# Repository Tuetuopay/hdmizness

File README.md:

# hdmizness

A business card that runs Linux and that has an HDMI output.

## Project layout

```
.
+- documentation       - docs for various chips and boards used
+- graphics            - various graphic files used for the hardware design
+- hardware            - home of the hardware design files
|  `- licheedmi        - PoC board that leverages a Lichee Pi Nano to test the concept
|                        of a pcb-only hdmi female connector
`- software            - everything related to the software running on those boards
```

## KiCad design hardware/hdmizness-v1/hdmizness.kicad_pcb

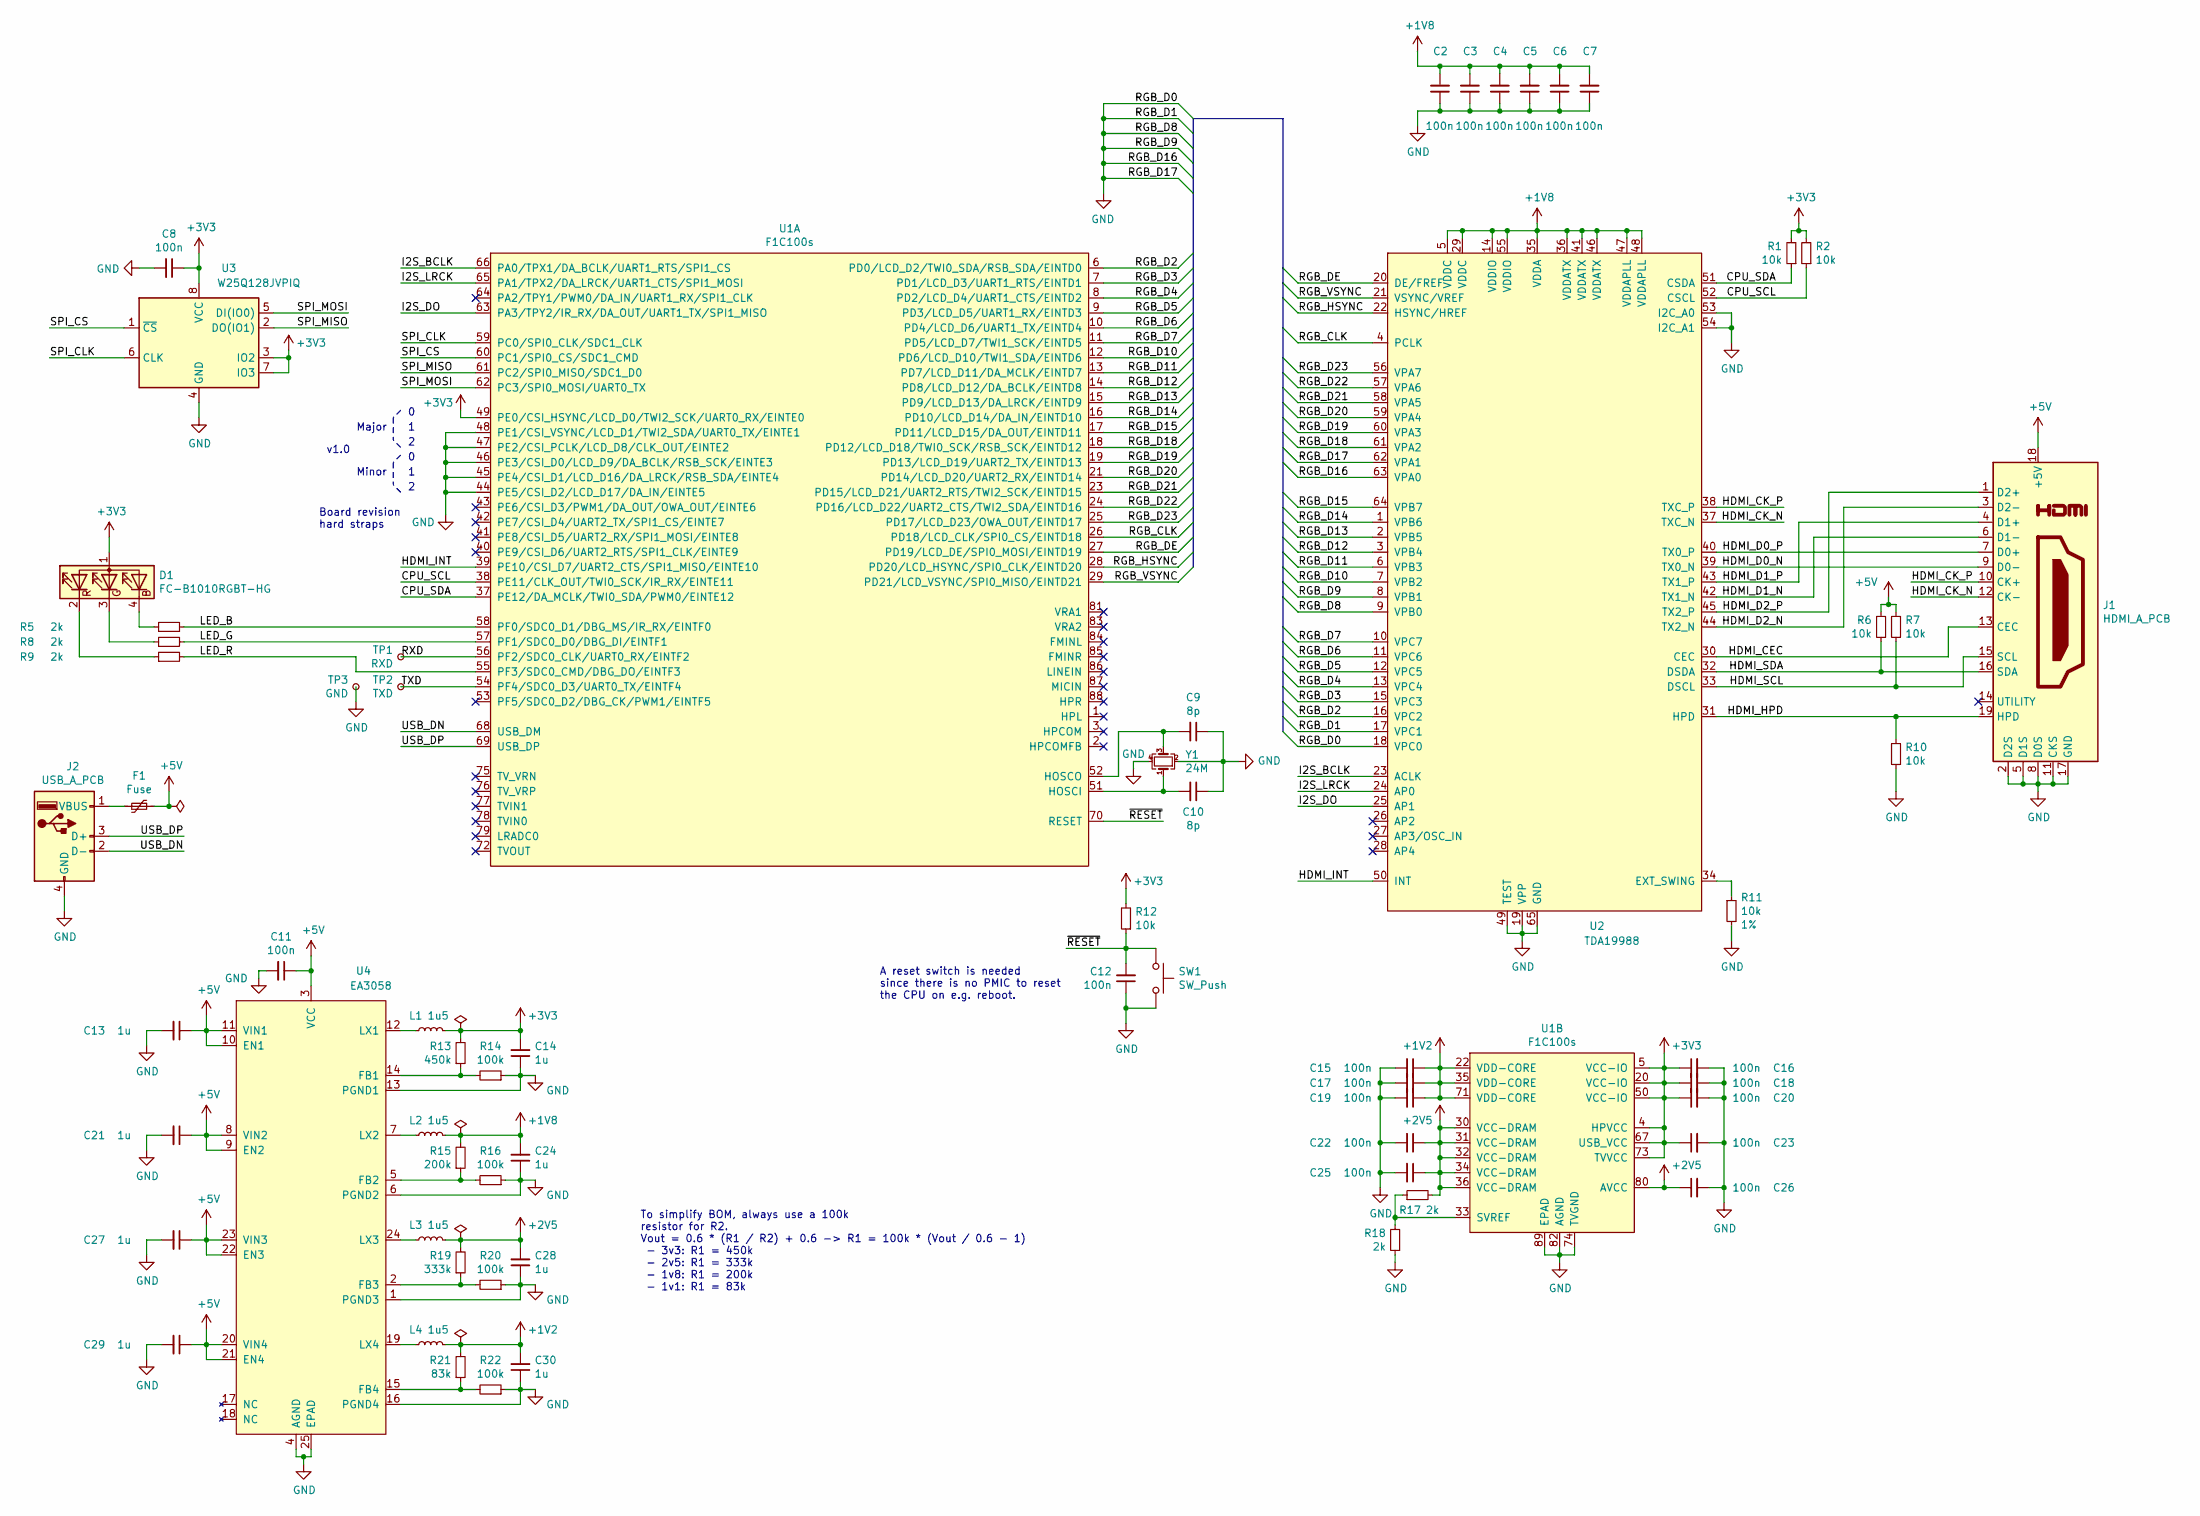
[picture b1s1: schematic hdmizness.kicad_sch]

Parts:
C2, C3, C4, C5, C6, C7, C8, C11, C12, C15, C16, C17, C18, C19, C20, C22, C23, C25, C26: 100n; C_0402_1005Metric; MFR P/N CL05B104KO5NNNC; LCSC P/N C1525
C9, C10: 8p; C_0402_1005Metric; MFR P/N CL05C080CB5NNNC; LCSC P/N C318586
C13, C14, C21, C24, C27, C28, C29, C30: 1u; C_0402_1005Metric; MFR P/N CL05A105KQ5NNNC; LCSC P/N C107372
D1: FC-B1010RGBT-HG; PLCC1010
F1: Fuse; Fuse_0603_1608Metric; MFR P/N 06H1100D; LCSC P/N C182303
J1: HDMI_A_PCB
J2: USB_A_PCB
L1, L2, L3, L4: 1u5; L_Vishay_IHHP-0806; MFR P/N CIGT201610UM1R5MNE; LCSC P/N C307630
R1, R2, R6, R7, R10, R12: 10k; R_0402_1005Metric; MFR P/N CR-02FL6---10K; LCSC P/N C406733
R5, R8, R9, R17, R18: 2k; R_0402_1005Metric; MFR P/N RC-02W2001FT; LCSC P/N C304583
R11: 10k; R_0402_1005Metric; Tolerance 1%; MFR P/N CR-02FL6---10K; LCSC P/N C406733
R13: 450k; R_0402_1005Metric; MFR P/N 0402WGF4503TCE; LCSC P/N C407681
R14, R16, R20, R22: 100k; R_0402_1005Metric; MFR P/N RC-02W1003FT; LCSC P/N C258090
R15: 200k; R_0402_1005Metric; MFR P/N WR04X2003FTL; LCSC P/N C305297
R19: 333k; R_0402_1005Metric; MFR P/N WR04X3323FTL; LCSC P/N C172051
R21: 83k; R_0402_1005Metric; MFR P/N RC-02W8202FT; LCSC P/N C304638
SW1: SW_Push; 1TS028A-2400-0603-CT; MFR P/N 1TS028A-2400-0603-CT; LCSC P/N C481994
TP1: RXD; TestPoint_Pad_1.0x1.0mm
TP2: TXD; TestPoint_Pad_1.0x1.0mm
TP3: GND; TestPoint_Pad_1.0x1.0mm
U1: F1C100s; QFN-88_EP_10x10_Pitch0.4mm
U2: TDA19988; QFN-64-1EP_9x9mm_P0.5mm_EP4.7x4.7mm
U3: W25Q128JVPIQ; WSON-8-1EP_6x5mm_P1.27mm_EP3.4x4.3mm; MFR P/N W25Q128JVPIQ; LCSC P/N C190862
U4: EA3058; QFN-24-1EP_4x4mm_P0.5mm_EP2.6x2.6mm; MFR P/N EA3058QDR; LCSC P/N C575412
Y1: 24M; Crystal_SMD_2016-4Pin_2.0x1.6mm; MFR P/N CN4024M00009T8188011; LCSC P/N C708986

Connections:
+1V2: C15.1, C17.1, C19.1, C30.2, L4.2, R21.2, U1.22 (VDD-CORE), U1.35 (VDD-CORE), U1.71 (VDD-CORE)
+1V8: C2.2, C3.2, C4.2, C5.2, C6.2, C7.2, C24.2, L2.2, R15.2, U2.5 (VDDC), U2.14 (VDDIO), U2.29 (VDDC), U2.35 (VDDA), U2.36 (VDDATX), U2.41 (VDDATX), U2.46 (VDDATX), U2.47 (VDDAPLL), U2.48 (VDDAPLL), U2.55 (VDDIO)
+2V5: C22.1, C25.1, C26.1, C28.2, L3.2, R17.2, R19.2, U1.30 (VCC-DRAM), U1.31 (VCC-DRAM), U1.32 (VCC-DRAM), U1.34 (VCC-DRAM), U1.36 (VCC-DRAM), U1.80 (AVCC)
+3V3: C8.1, C14.2, C16.1, C18.1, C20.1, C23.1, D1.1 (A), L1.2, R1.2, R2.2, R12.2, R13.2, U1.4 (HPVCC), U1.5 (VCC-IO), U1.20 (VCC-IO), U1.49 (PE0/CSI_HSYNC/LCD_D0/TWI2_SCK/UART0_RX/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), U1.50 (VCC-IO), U1.67 (USB_VCC), U1.73 (TVVCC), U3.3 (IO2), U3.7 (IO3), U3.8 (VCC)
+5V: C11.1, C13.1, C21.1, C27.1, C29.1, F1.1, J1.18 (+5V), R6.2, R7.2, U4.3 (VCC), U4.8 (VIN2), U4.9 (EN2), U4.10 (EN1), U4.11 (VIN1), U4.20 (VIN4), U4.21 (EN4), U4.22 (EN3), U4.23 (VIN3)
/CPU_SCL: R2.1, U1.38 (PE11/CLK_OUT/TWI0_SCK/IR_RX/EINTE11), U2.52 (CSCL)
/CPU_SDA: R1.1, U1.37 (PE12/DA_MCLK/TWI0_SDA/PWM0/EINTE12), U2.51 (CSDA)
/HDMI_CEC: J1.13 (CEC), U2.30 (CEC)
/HDMI_CK_N: J1.12 (CK-), U2.37 (TXC_N)
/HDMI_CK_P: J1.10 (CK+), U2.38 (TXC_P)
/HDMI_D0_N: J1.9 (D0-), U2.39 (TX0_N)
/HDMI_D0_P: J1.7 (D0+), U2.40 (TX0_P)
/HDMI_D1_N: J1.6 (D1-), U2.42 (TX1_N)
/HDMI_D1_P: J1.4 (D1+), U2.43 (TX1_P)
/HDMI_D2_N: J1.3 (D2-), U2.44 (TX2_N)
/HDMI_D2_P: J1.1 (D2+), U2.45 (TX2_P)
/HDMI_HPD: J1.19 (HPD), R10.2, U2.31 (HPD)
/HDMI_INT: U1.39 (PE10/CSI_D7/UART2_CTS/SPI1_MISO/EINTE10), U2.50 (INT)
/HDMI_SCL: J1.15 (SCL), R7.1, U2.33 (DSCL)
/HDMI_SDA: J1.16 (SDA), R6.1, U2.32 (DSDA)
/I2S_BCLK: U1.66 (PA0/TPX1/DA_BCLK/UART1_RTS/SPI1_CS), U2.23 (ACLK)
/I2S_DO: U1.63 (PA3/TPY2/IR_RX/DA_OUT/UART1_TX/SPI1_MISO), U2.25 (AP1)
/I2S_LRCK: U1.65 (PA1/TPX2/DA_LRCK/UART1_CTS/SPI1_MOSI), U2.24 (AP0)
/LED_B: R5.2, U1.58 (PF0/SDC0_D1/DBG_MS/IR_RX/EINTF0)
/LED_G: R8.2, U1.57 (PF1/SDC0_D0/DBG_DI/EINTF1)
/LED_R: R9.2, U1.55 (PF3/SDC0_CMD/DBG_DO/EINTF3)
/RGB_CLK: U1.26 (PD18/LCD_CLK/SPI0_CS/EINTD18), U2.4 (PCLK)
/RGB_D2: U1.6 (PD0/LCD_D2/TWI0_SDA/RSB_SDA/EINTD0), U2.16 (VPC2)
/RGB_D3: U1.7 (PD1/LCD_D3/UART1_RTS/EINTD1), U2.15 (VPC3)
/RGB_D4: U1.8 (PD2/LCD_D4/UART1_CTS/EINTD2), U2.13 (VPC4)
/RGB_D5: U1.9 (PD3/LCD_D5/UART1_RX/EINTD3), U2.12 (VPC5)
/RGB_D6: U1.10 (PD4/LCD_D6/UART1_TX/EINTD4), U2.11 (VPC6)
/RGB_D7: U1.11 (PD5/LCD_D7/TWI1_SCK/EINTD5), U2.10 (VPC7)
/RGB_D10: U1.12 (PD6/LCD_D10/TWI1_SDA/EINTD6), U2.7 (VPB2)
/RGB_D11: U1.13 (PD7/LCD_D11/DA_MCLK/EINTD7), U2.6 (VPB3)
/RGB_D12: U1.14 (PD8/LCD_D12/DA_BCLK/EINTD8), U2.3 (VPB4)
/RGB_D13: U1.15 (PD9/LCD_D13/DA_LRCK/EINTD9), U2.2 (VPB5)
/RGB_D14: U1.16 (PD10/LCD_D14/DA_IN/EINTD10), U2.1 (VPB6)
/RGB_D15: U1.17 (PD11/LCD_D15/DA_OUT/EINTD11), U2.64 (VPB7)
/RGB_D18: U1.18 (PD12/LCD_D18/TWI0_SCK/RSB_SCK/EINTD12), U2.61 (VPA2)
/RGB_D19: U1.19 (PD13/LCD_D19/UART2_TX/EINTD13), U2.60 (VPA3)
/RGB_D20: U1.21 (PD14/LCD_D20/UART2_RX/EINTD14), U2.59 (VPA4)
/RGB_D21: U1.23 (PD15/LCD_D21/UART2_RTS/TWI2_SCK/EINTD15), U2.58 (VPA5)
/RGB_D22: U1.24 (PD16/LCD_D22/UART2_CTS/TWI2_SDA/EINTD16), U2.57 (VPA6)
/RGB_D23: U1.25 (PD17/LCD_D23/OWA_OUT/EINTD17), U2.56 (VPA7)
/RGB_DE: U1.27 (PD19/LCD_DE/SPI0_MOSI/EINTD19), U2.20 (DE/FREF)
/RGB_HSYNC: U1.28 (PD20/LCD_HSYNC/SPI0_CLK/EINTD20), U2.22 (HSYNC/HREF)
/RGB_VSYNC: U1.29 (PD21/LCD_VSYNC/SPI0_MISO/EINTD21), U2.21 (VSYNC/VREF)
/RXD: TP1.1, U1.56 (PF2/SDC0_CLK/UART0_RX/EINTF2)
/SPI_CLK: U1.59 (PC0/SPI0_CLK/SDC1_CLK), U3.6 (CLK)
/SPI_CS: U1.60 (PC1/SPI0_CS/SDC1_CMD), U3.1 (~CS)
/SPI_MISO: U1.61 (PC2/SPI0_MISO/SDC1_D0), U3.2 (DO(IO1))
/SPI_MOSI: U1.62 (PC3/SPI0_MOSI/UART0_TX), U3.5 (DI(IO0))
/TXD: TP2.1, U1.54 (PF4/SDC0_D3/UART0_TX/EINTF4)
/USB_DN: J2.2 (D-), U1.68 (USB_DM)
/USB_DP: J2.3 (D+), U1.69 (USB_DP)
/~RESET: C12.2, R12.1, SW1.1, U1.70 (RESET)
GND: C2.1, C3.1, C4.1, C5.1, C6.1, C7.1, C8.2, C9.1, C10.1, C11.2, C12.1, C13.2, C14.1, C15.2, C16.2, C17.2, C18.2, C19.2, C20.2, C21.2, C22.2, C23.2, C24.1, C25.2, C26.2, C27.2, C28.1, C29.2, C30.1, J1.2 (D2S), J1.5 (D1S), J1.8 (D0S), J1.11 (CKS), J1.17 (GND), J2.4 (GND), R10.1, R11.2, R14.1, R16.1, R18.1, R20.1, R22.1, SW1.2, TP3.1, U1.44 (PE5/CSI_D2/LCD_D17/DA_IN/EINTE5), U1.45 (PE4/CSI_D1/LCD_D16/DA_LRCK/RSB_SDA/EINT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), U1.46 (PE3/CSI_D0/LCD_D9/DA_BCLK/RSB_SCK/EINTE3), U1.47 (PE2/CSI_PCLK/LCD_D8/CLK_OUT/EINTE2), U1.48 (PE1/CSI_VSYNC/LCD_D1/TWI2_SDA/UART0_TX/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), U1.74 (TVGND), U1.82 (AGND), U1.89 (EPAD), U2.8 (VPB1), U2.9 (VPB0), U2.17 (VPC1), U2.18 (VPC0), U2.19 (VPP), U2.49 (TEST), U2.53 (I2C_A0), U2.54 (I2C_A1), U2.62 (VPA1), U2.63 (VPA0), U2.65 (GND), U3.4 (GND), U4.1 (PGND3), U4.4 (AGND), U4.6 (PGND2), U4.13 (PGND1), U4.16 (PGND4), U4.25 (EPAD), Y1.2, Y1.4
unnamed: D1.4 (BK), R5.1
unnamed: D1.3 (GK), R8.1
unnamed: D1.2 (RK), R9.1
unnamed: F1.2, J2.1 (VBUS)
unnamed: C10.2, U1.51 (HOSCI), Y1.1
unnamed: C9.2, U1.52 (HOSCO), Y1.3
unnamed: R17.1, R18.2, U1.33 (SVREF)
unnamed: R11.1, U2.34 (EXT_SWING)
unnamed: R13.1, R14.2, U4.14 (FB1)
unnamed: R15.1, R16.2, U4.5 (FB2)
unnamed: R19.1, R20.2, U4.2 (FB3)
unnamed: R21.1, R22.2, U4.15 (FB4)
unnamed: L1.1, U4.12 (LX1)
unnamed: L2.1, U4.7 (LX2)
unnamed: L3.1, U4.24 (LX3)
unnamed: L4.1, U4.19 (LX4)

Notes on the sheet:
Minor
Major
v1.0
To simplify BOM, always use a 100k resistor for R2. Vout = 0.6 * (R1 / R2) + 0.6 -> R1 = 100k * (Vout / 0.6 - 1) - 3v3: R1 = 450k - 2v5: R1 = 333k - 1v8: R1 = 200k - 1v1: R1 = 83k
Board revision hard straps
A reset switch is needed since there is no PMIC to reset the CPU on e.g. reboot.

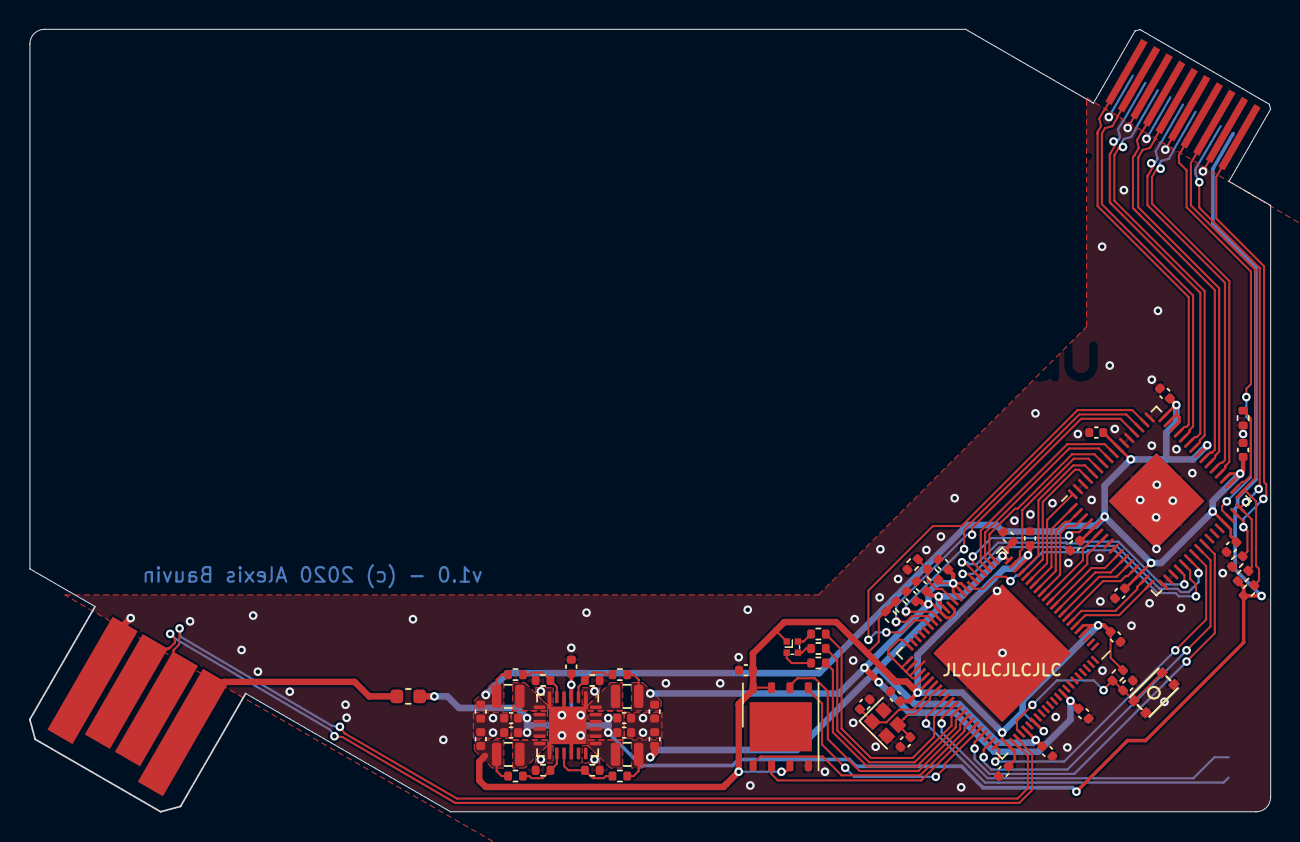
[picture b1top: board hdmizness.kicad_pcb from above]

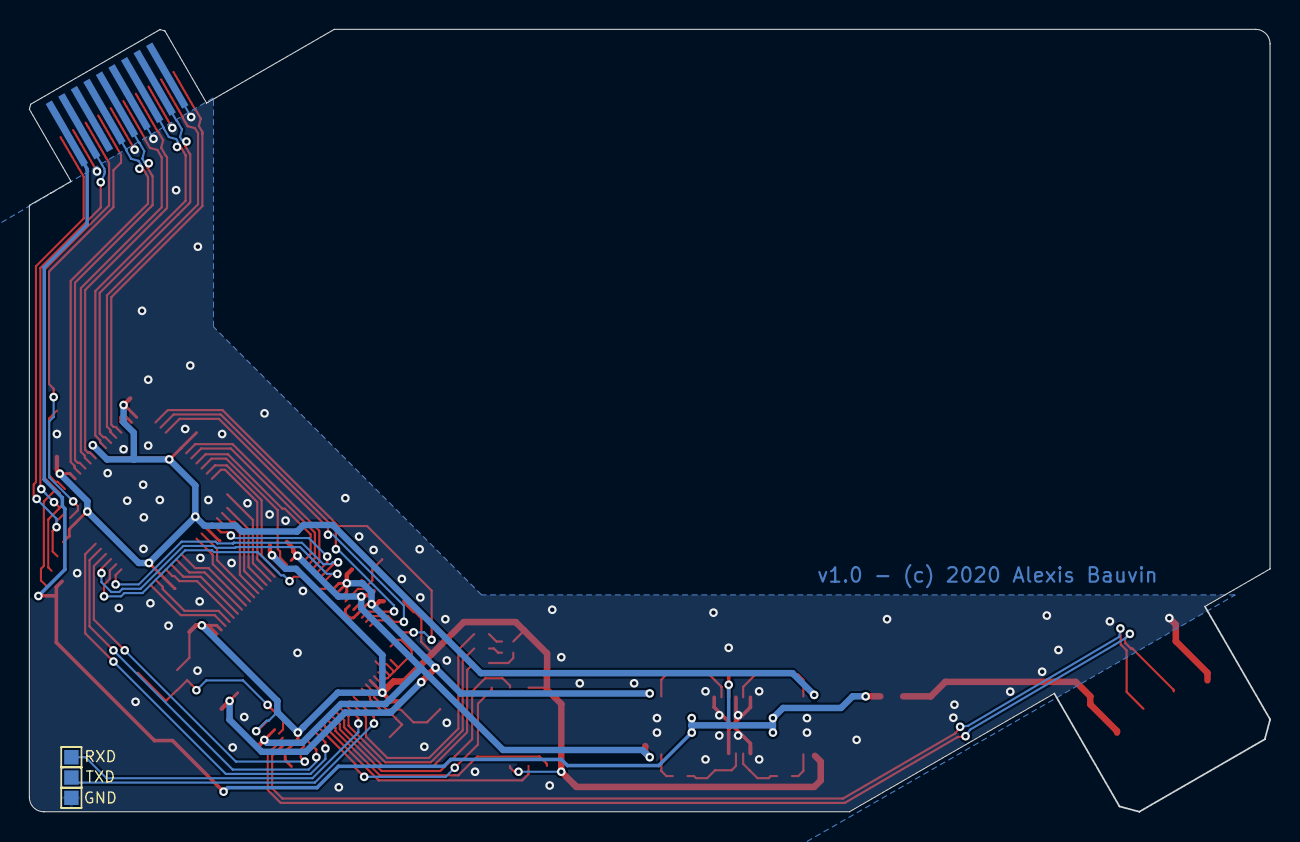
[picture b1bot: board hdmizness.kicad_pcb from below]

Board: 2 copper layers, 85.6 x 53.9 mm, 67 parts (3 on the bottom side), 74 nets.

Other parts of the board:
Ref**: Val**; card_front

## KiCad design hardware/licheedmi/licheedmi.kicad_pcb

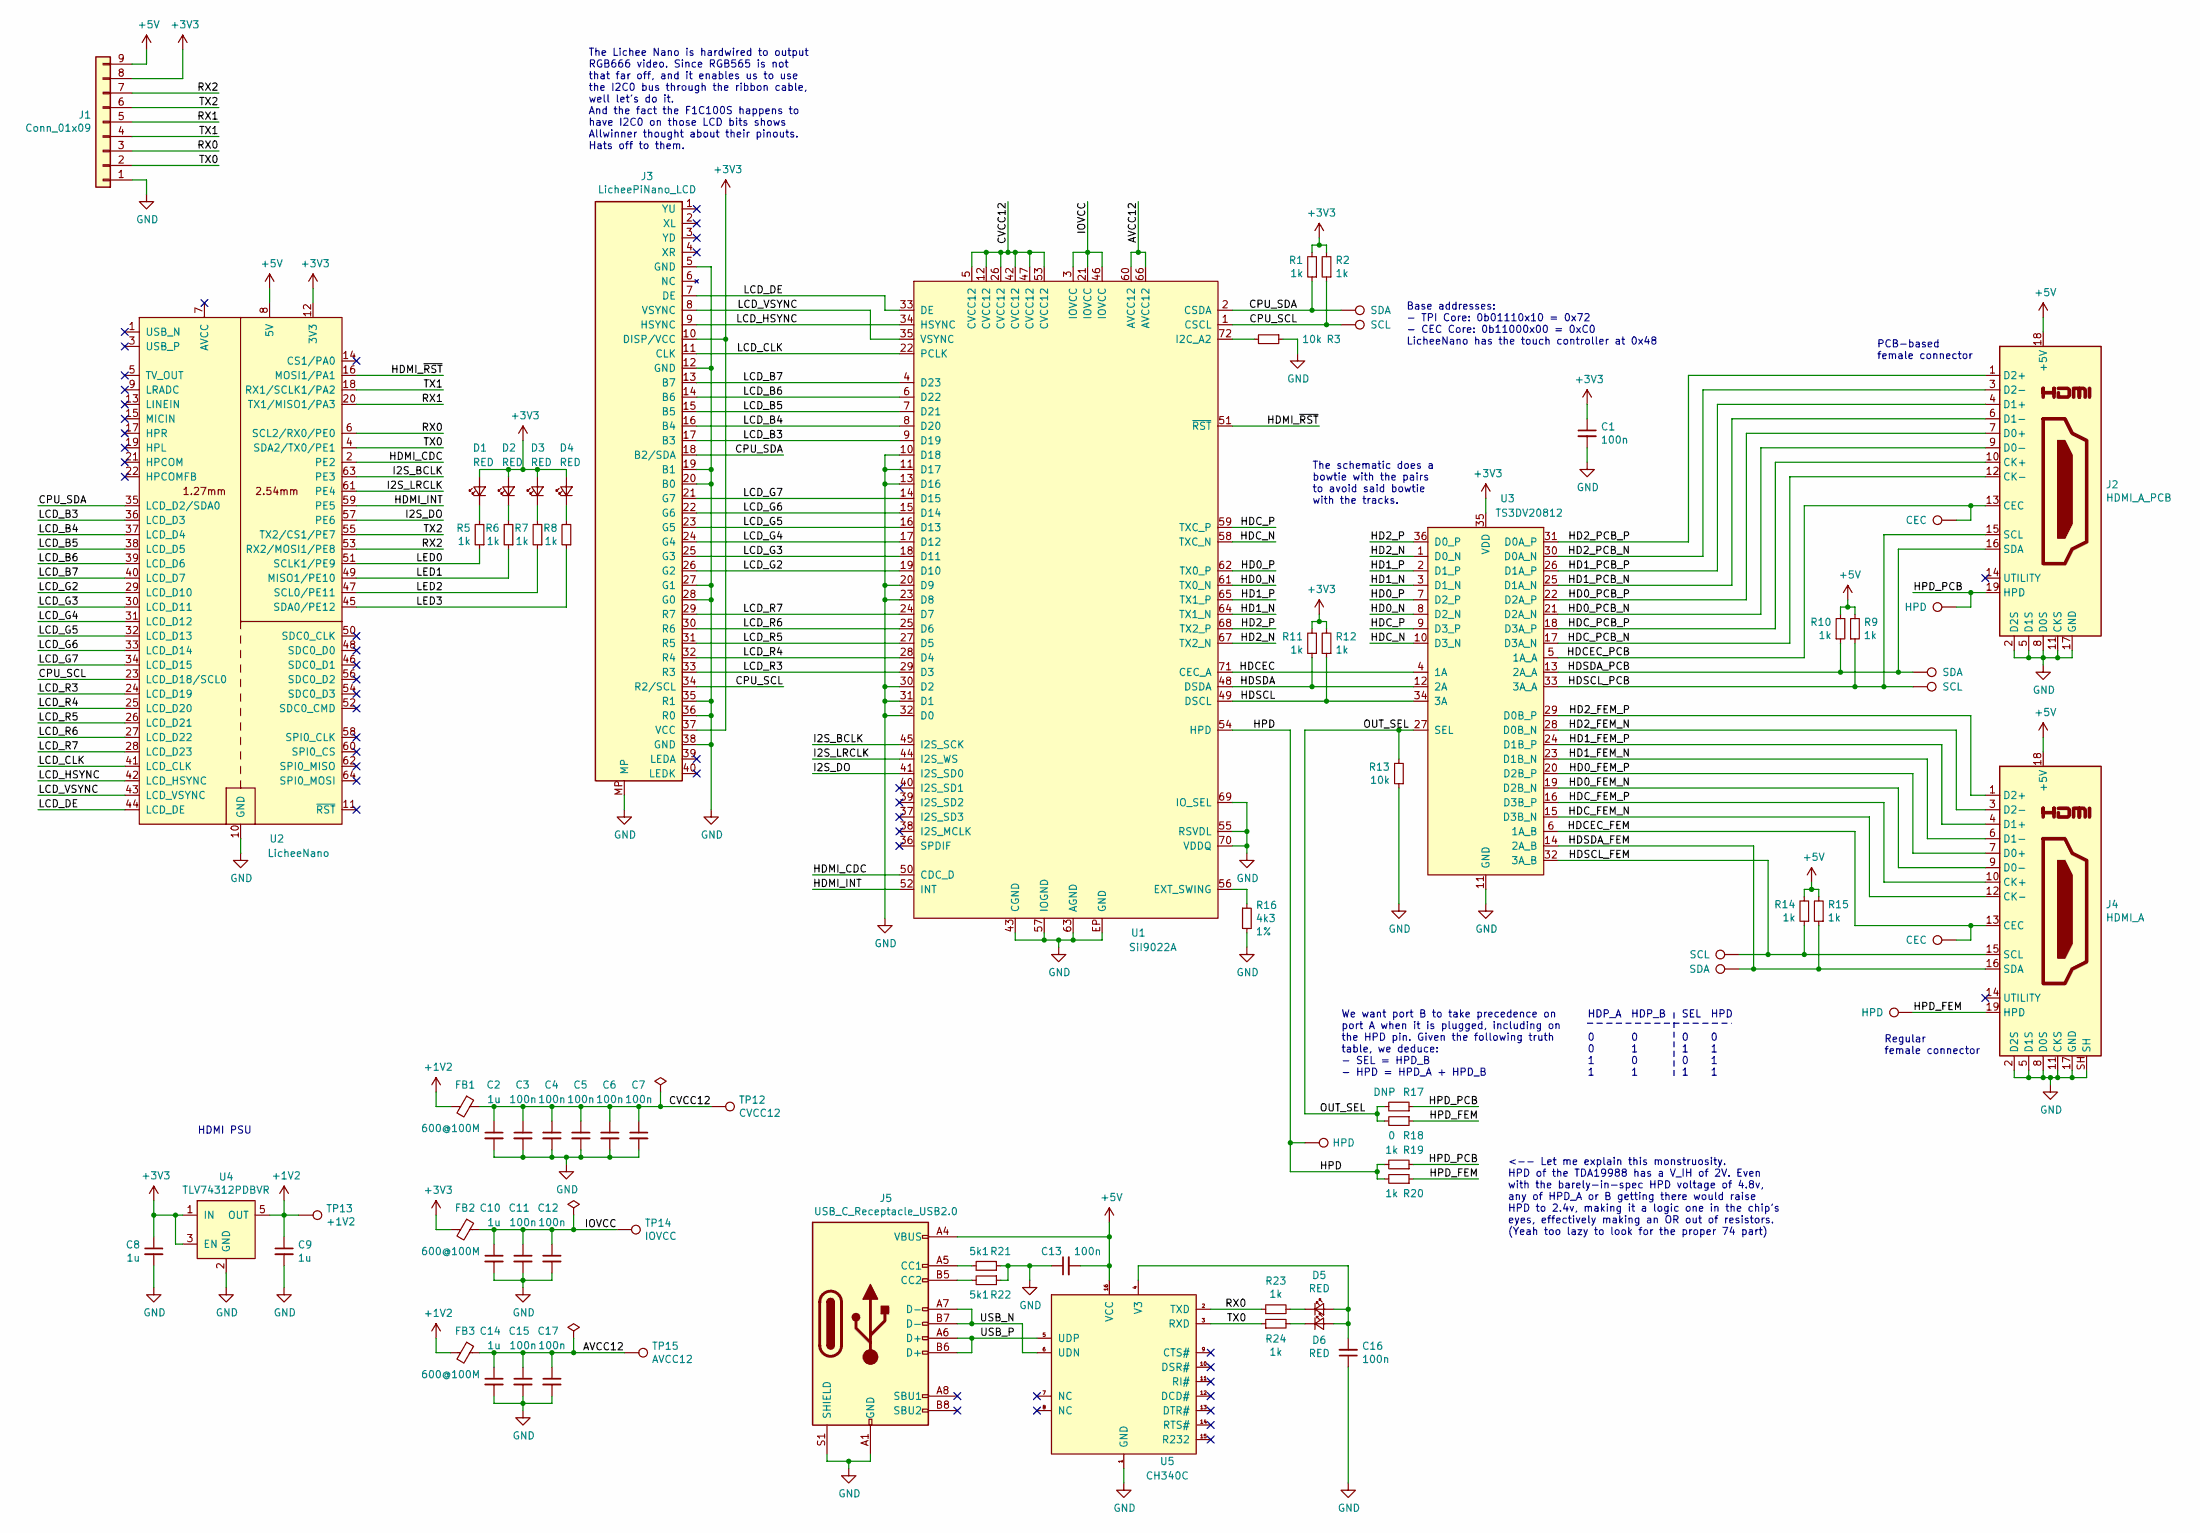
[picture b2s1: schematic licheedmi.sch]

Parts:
C1, C3, C4, C5, C6, C7, C11, C12, C13, C15, C16, C17: 100n; C_0603_1608Metric; MFR P/N CL10B104KB8NNNC; LCSC P/N C1591
C2, C8, C9, C10, C14: 1u; C_0603_1608Metric; MFR P/N CL10B105KP8NNNC; LCSC P/N C95843
D1, D2, D3, D4, D5, D6: RED; LED_0603_1608Metric; MFR P/N LTST-C193KRKT-5A; LCSC P/N C157741
FB1, FB2, FB3: 600@100M; L_0603_1608Metric; MFR P/N MMZ1608Y601BTA00; LCSC P/N C136491
J1: Conn_01x09; PinHeader_1x09_P2.54mm_Vertical; MFR P/N A2541WV-9P; LCSC P/N C225484
J2: HDMI_A_PCB
J3: LicheePiNano_LCD; Hirose_FH12-40S-0.5SH_1x40-1MP_P0.50mm_Horizontal; MFR P/N FH12-40S-0.5SH(55); LCSC P/N C202114
J4: HDMI_A; Boomelec_HDMI-001; MFR P/N HDMI-001; LCSC P/N C138388
J5: USB_C_Receptacle_USB2.0; USB_C_Receptacle_Palconn_UTC16-G; MFR P/N TYPE-C-31-M-12; LCSC P/N C165948
R1, R2, R5, R6, R7, R8, R9, R10, R11, R12, R14, R15, R19, R20, R23, R24: 1k; R_0603_1608Metric; MFR P/N SY0603JN1KP; LCSC P/N C380759
R3, R13: 10k; R_0603_1608Metric; MFR P/N RC0603FR-0710KL; LCSC P/N C98220
R16: 4k3; R_0603_1608Metric; Tolerance 1%; MFR P/N 0603WAF4301T5E; LCSC P/N C23159
R17: DNP; R_0603_1608Metric
R18: 0; R_0603_1608Metric; MFR P/N WR06X000PTL; LCSC P/N C132607
R21, R22: 5k1; R_0603_1608Metric; MFR P/N RS-03K5101FT; LCSC P/N C156350
TP1, TP5: CEC; TestPoint_Pad_D1.0mm
TP2, TP6, TP10: SCL; TestPoint_Pad_D1.0mm
TP3, TP7, TP11: SDA; TestPoint_Pad_D1.0mm
TP4, TP8, TP9: HPD; TestPoint_Pad_D1.0mm
TP12: CVCC12; TestPoint_Pad_D1.0mm
TP13: +1V2; TestPoint_Pad_D1.0mm
TP14: IOVCC; TestPoint_Pad_D1.0mm
TP15: AVCC12; TestPoint_Pad_D1.0mm
U1: SiI9022A; QFN-72-1EP_10x10mm_P0.5mm_EP4.7x4.7mm_ThermalVias; MFR P/N SII9022ACNU; LCSC P/N C369565
U2: LicheeNano; MFR P/N C35445; LCSC P/N C35445
U3: TS3DV20812; QFN-36-1EP_6x6mm_P0.5mm_EP4.1x4.1mm; MFR P/N TS3DV20812RHHR; LCSC P/N C130083
U4: TLV74312PDBVR; TSOT-23-5; MFR P/N TLV74312PDBVR; LCSC P/N C485149
U5: CH340C; SOIC-16_3.9x9.9mm_P1.27mm; MFR P/N CH340C; LCSC P/N C84681

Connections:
+1V2: C9.1, FB1.2, FB3.2, TP13.1, U4.5 (OUT)
+3V3: C1.1, C8.1, D1.2 (A), D2.2 (A), D3.2 (A), D4.2 (A), FB2.2, J1.8, J3.10 (DISP/VCC), J3.37 (VCC), R1.2, R2.2, R11.2, R12.2, U2.12 (3V3), U3.35 (VDD), U4.1 (IN), U4.3 (EN)
+5V: C13.2, J1.9, J2.18 (+5V), J4.18 (+5V), J5.A4 (VBUS), J5.A9 (VBUS), J5.B4 (VBUS), J5.B9 (VBUS), R9.2, R10.2, R14.2, R15.2, U2.8 (5V), U5.16 (VCC)
/AVCC12: C14.1, C15.1, C17.1, FB3.1, TP15.1, U1.60 (AVCC12), U1.66 (AVCC12)
/CPU_SCL: J3.34 (R2/SCL), R2.1, TP10.1, U1.1 (CSCL), U2.23 (LCD_D18/SCL0)
/CPU_SDA: J3.18 (B2/SDA), R1.1, TP11.1, U1.2 (CSDA), U2.35 (LCD_D2/SDA0)
/CVCC12: C2.1, C3.1, C4.1, C5.1, C6.1, C7.1, FB1.1, TP12.1, U1.5 (CVCC12), U1.12 (CVCC12), U1.26 (CVCC12), U1.42 (CVCC12), U1.47 (CVCC12), U1.53 (CVCC12)
/HD0_FEM_N: J4.9 (D0-), U3.19 (D2B_N)
/HD0_FEM_P: J4.7 (D0+), U3.20 (D2B_P)
/HD0_N: U1.61 (TX0_N), U3.8 (D2_N)
/HD0_P: U1.62 (TX0_P), U3.7 (D2_P)
/HD0_PCB_N: J2.9 (D0-), U3.21 (D2A_N)
/HD0_PCB_P: J2.7 (D0+), U3.22 (D2A_P)
/HD1_FEM_N: J4.6 (D1-), U3.23 (D1B_N)
/HD1_FEM_P: J4.4 (D1+), U3.24 (D1B_P)
/HD1_N: U1.64 (TX1_N), U3.3 (D1_N)
/HD1_P: U1.65 (TX1_P), U3.2 (D1_P)
/HD1_PCB_N: J2.6 (D1-), U3.25 (D1A_N)
/HD1_PCB_P: J2.4 (D1+), U3.26 (D1A_P)
/HD2_FEM_N: J4.3 (D2-), U3.28 (D0B_N)
/HD2_FEM_P: J4.1 (D2+), U3.29 (D0B_P)
/HD2_N: U1.67 (TX2_N), U3.1 (D0_N)
/HD2_P: U1.68 (TX2_P), U3.36 (D0_P)
/HD2_PCB_N: J2.3 (D2-), U3.30 (D0A_N)
/HD2_PCB_P: J2.1 (D2+), U3.31 (D0A_P)
/HDCEC: U1.71 (CEC_A), U3.4 (1A)
/HDCEC_FEM: J4.13 (CEC), TP5.1, U3.6 (1A_B)
/HDCEC_PCB: J2.13 (CEC), TP1.1, U3.5 (1A_A)
/HDC_FEM_N: J4.12 (CK-), U3.15 (D3B_N)
/HDC_FEM_P: J4.10 (CK+), U3.16 (D3B_P)
/HDC_N: U1.58 (TXC_N), U3.10 (D3_N)
/HDC_P: U1.59 (TXC_P), U3.9 (D3_P)
/HDC_PCB_N: J2.12 (CK-), U3.17 (D3A_N)
/HDC_PCB_P: J2.10 (CK+), U3.18 (D3A_P)
/HDMI_CDC: U1.50 (CDC_D), U2.2 (PE2)
/HDMI_INT: U1.52 (INT), U2.59 (PE5)
/HDMI_~RST: U1.51 (~RST), U2.16 (MOSI1/PA1)
/HDSCL: R12.1, U1.49 (DSCL), U3.34 (3A)
/HDSCL_FEM: J4.15 (SCL), R14.1, TP6.1, U3.32 (3A_B)
/HDSCL_PCB: J2.15 (SCL), R9.1, TP2.1, U3.33 (3A_A)
/HDSDA: R11.1, U1.48 (DSDA), U3.12 (2A)
/HDSDA_FEM: J4.16 (SDA), R15.1, TP7.1, U3.14 (2A_B)
/HDSDA_PCB: J2.16 (SDA), R10.1, TP3.1, U3.13 (2A_A)
/HPD: R19.2, R20.2, TP9.1, U1.54 (HPD)
/HPD_FEM: J4.19 (HPD), R18.1, R20.1, TP8.1
/HPD_PCB: J2.19 (HPD), R17.1, R19.1, TP4.1
/I2S_BCLK: U1.45 (I2S_SCK), U2.63 (PE3)
/I2S_DO: U1.41 (I2S_SD0), U2.57 (PE6)
/I2S_LRCLK: U1.44 (I2S_WS), U2.61 (PE4)
/IOVCC: C10.1, C11.1, C12.1, FB2.1, TP14.1, U1.3 (IOVCC), U1.21 (IOVCC), U1.46 (IOVCC)
/LCD_B3: J3.17 (B3), U1.9 (D19), U2.36 (LCD_D3)
/LCD_B4: J3.16 (B4), U1.8 (D20), U2.37 (LCD_D4)
/LCD_B5: J3.15 (B5), U1.7 (D21), U2.38 (LCD_D5)
/LCD_B6: J3.14 (B6), U1.6 (D22), U2.39 (LCD_D6)
/LCD_B7: J3.13 (B7), U1.4 (D23), U2.40 (LCD_D7)
/LCD_CLK: J3.11 (CLK), U1.22 (PCLK), U2.41 (LCD_CLK)
/LCD_DE: J3.7 (DE), U1.33 (DE), U2.44 (LCD_DE)
/LCD_G2: J3.26 (G2), U1.19 (D10), U2.29 (LCD_D10)
/LCD_G3: J3.25 (G3), U1.18 (D11), U2.30 (LCD_D11)
/LCD_G4: J3.24 (G4), U1.17 (D12), U2.31 (LCD_D12)
/LCD_G5: J3.23 (G5), U1.16 (D13), U2.32 (LCD_D13)
/LCD_G6: J3.22 (G6), U1.15 (D14), U2.33 (LCD_D14)
/LCD_G7: J3.21 (G7), U1.14 (D15), U2.34 (LCD_D15)
/LCD_HSYNC: J3.9 (HSYNC), U1.34 (HSYNC), U2.42 (LCD_HSYNC)
/LCD_R3: J3.33 (R3), U1.29 (D3), U2.24 (LCD_D19)
/LCD_R4: J3.32 (R4), U1.28 (D4), U2.25 (LCD_D20)
/LCD_R5: J3.31 (R5), U1.27 (D5), U2.26 (LCD_D21)
/LCD_R6: J3.30 (R6), U1.25 (D6), U2.27 (LCD_D22)
/LCD_R7: J3.29 (R7), U1.24 (D7), U2.28 (LCD_D23)
/LCD_VSYNC: J3.8 (VSYNC), U1.35 (VSYNC), U2.43 (LCD_VSYNC)
/LED0: R5.1, U2.51 (SCLK1/PE9)
/LED1: R6.1, U2.49 (MISO1/PE10)
/LED2: R7.1, U2.47 (SCL0/PE11)
/LED3: R8.1, U2.45 (SDA0/PE12)
/OUT_SEL: R13.2, R17.2, R18.2, U3.27 (SEL)
/RX0: J1.3, R23.1, U2.6 (SCL2/RX0/PE0), U5.2 (TXD)
/RX1: J1.5, U2.20 (TX1/MISO1/PA3)
/RX2: J1.7, U2.53 (RX2/MOSI1/PE8)
/TX0: J1.2, R24.1, U2.4 (SDA2/TX0/PE1), U5.3 (RXD)
/TX1: J1.4, U2.18 (RX1/SCLK1/PA2)
/TX2: J1.6, U2.55 (TX2/CS1/PE7)
/USB_N: J5.A7 (D-), J5.B7 (D-), U5.6 (UDN)
/USB_P: J5.A6 (D+), J5.B6 (D+), U5.5 (UDP)
GND: C1.2, C2.2, C3.2, C4.2, C5.2, C6.2, C7.2, C8.2, C9.2, C10.2, C11.2, C12.2, C13.1, C14.2, C15.2, C16.1, C17.2, J1.1, J2.2 (D2S), J2.5 (D1S), J2.8 (D0S), J2.11 (CKS), J2.17 (GND), J3.5 (GND), J3.12 (GND), J3.19 (B1), J3.20 (B0), J3.27 (G1), J3.28 (G0), J3.35 (R1), J3.36 (R0), J3.38 (GND), J3.MP, J4.2 (D2S), J4.5 (D1S), J4.8 (D0S), J4.11 (CKS), J4.17 (GND), J4.SH, J5.A1 (GND), J5.A12 (GND), J5.B1 (GND), J5.B12 (GND), J5.S1 (SHIELD), R3.1, R13.1, R16.2, R21.1, R22.1, U1.10 (D18), U1.11 (D17), U1.13 (D16), U1.20 (D9), U1.23 (D8), U1.30 (D2), U1.31 (D1), U1.32 (D0), U1.43 (CGND), U1.55 (RSVDL), U1.57 (IOGND), U1.63 (AGND), U1.69 (IO_SEL), U1.70 (VDDQ), U1.EP (GND), U2.10 (GND), U3.11 (GND), U4.2 (GND), U5.1 (GND)
unnamed: C16.2, D5.2 (A), D6.2 (A), U5.4 (V3)
unnamed: D1.1 (K), R5.2
unnamed: D2.1 (K), R6.2
unnamed: D3.1 (K), R7.2
unnamed: D4.1 (K), R8.2
unnamed: D5.1 (K), R23.2
unnamed: D6.1 (K), R24.2
unnamed: J5.A5 (CC1), R21.2
unnamed: J5.B5 (CC2), R22.2
unnamed: R3.2, U1.72 (I2C_A2)
unnamed: R16.1, U1.56 (EXT_SWING)

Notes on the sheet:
Base addresses: - TPI Core: 0b01110x10 = 0x72 - CEC Core: 0b11000x00 = 0xC0 LicheeNano has the touch controller at 0x48
The schematic does a bowtie with the pairs to avoid said bowtie with the tracks.
PCB-based female connector
Regular female connector
HDMI PSU
We want port B to take precedence on port A when it is plugged, including on the HPD pin. Given the following truth table, we deduce: - SEL = HPD_B - HPD = HPD_A + HPD_B
HDP_A 0 0 1 1
HDP_B 0 1 0 1
SEL 0 1 0 1
HPD 0 1 1 1
<-- Let me explain this monstruosity. HPD of the TDA19988 has a V_IH of 2V. Even with the barely-in-spec HPD voltage of 4.8v, any of HPD_A or B getting there would raise HPD to 2.4v, making it a logic one in the chip's eyes, effectively making an OR out of resistors. (Yeah too lazy to look for the 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
The Lichee Nano is hardwired to output RGB666 video. Since RGB565 is not that far off, and it enables us to use the I2C0 bus through the ribbon cable, well let's do it. And the fact the F1C100S happens to have I2C0 on those LCD bits shows Allwinner thought about their pinouts. Hats off to them.

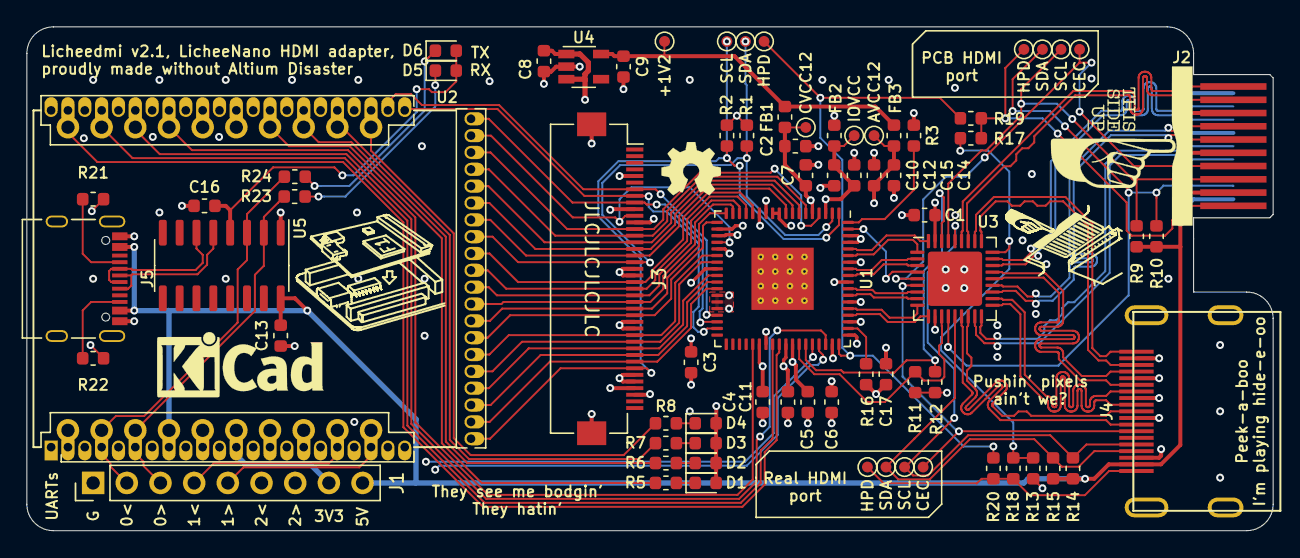
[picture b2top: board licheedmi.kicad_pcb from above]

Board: 4 copper layers, 94.0 x 38.0 mm, 74 parts (0 on the bottom side), 95 nets.

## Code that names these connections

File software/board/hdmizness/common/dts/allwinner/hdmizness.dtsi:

/*
 * Copyright (C) 2020 Tuetuopay <tuetuopay@me.com>
 *
 * SPDX-License-Identifier: (GPL-2.0+ OR X11)
 */

/dts-v1/;
#include "suniv-f1c100s.dtsi"
#include <dt-bindings/gpio/gpio.h>

/ {
	model = "HDMIzness";
	compatible = "tuetuopay,hdmizness", "allwinner,suniv-f1c100s";

	aliases {
		serial0 = &uart0;
		spi0 = &spi0;
	};

	chosen {
		stdout-path = "serial0:115200n8";
	};

	leds {
		compatible = "gpio-leds";
		pinctrl-names = "default";
		pinctrl-0 = <&led_pins>;

		red {
			label = "red";
			gpios = <&pio 5 3 GPIO_ACTIVE_LOW>;
			default-state = "on";
		};

		green {
			label = "green";
			gpios = <&pio 5 1 GPIO_ACTIVE_LOW>;
			default-state = "on";
		};

		blue {
			label = "blue";
			gpios = <&pio 5 0 GPIO_ACTIVE_LOW>;
			default-state = "on";
		};
	};

	reg_vcc3v3: vcc3v3 {
		compatible = "regulator-fixed";
		regulator-name = "vcc3v3";
		regulator-min-microvolt = <3300000>;
		regulator-max-microvolt = <3300000>;
	};
};

&pio {
	uart0_pf_pins: uart0-pf-pins {
		pins = "PF2", "PF4";
		function = "uart0";
	};

	led_pins: led-pins {
		pins = "PF0", "PF1", "PF3";
		function = "gpio_out";
	};

	i2c0_pe_pins: i2c0-pe-pins {
		pins = "PE11", "PE12";
		function = "i2c0";
	};
};

&otg_sram {
	status = "okay";
};

&spi0 {
	pinctrl-names = "default";
	pinctrl-0 = <&spi0_pc_pins>;
	status = "okay";

	flash@0 {
		#address-cells = <1>;
		#size-cells = <1>;
		compatible = "winbond,w25q128", "jedec,spi-nor";
		reg = <0>;
		spi-max-frequency = <40000000>;

		partitions {
			compatible = "fixed-partitions";
			#address-cells = <1>;
			#size-cells = <1>;

			partition@0 {
				label = "u-boot";
				reg = <0x000000 0x80000>;
			};

			partition@110000 {
				label = "rootubi";
				reg = <0x80000 0xf80000>;
			};
		};
	};
};

&uart0 {
	pinctrl-names = "default";
	pinctrl-0 = <&uart0_pf_pins>;
	status = "okay";
};

&i2c0 {
	pinctrl-names = "default";
	pinctrl-0 = <&i2c0_pe_pins>;
	status = "okay";
};

&usb_otg {
	dr_mode = "peripheral";
	status = "okay";
};

&usbphy {
	usb0_id_det-gpio = <&pio 4 6 GPIO_ACTIVE_HIGH>; /* PE6 */
	status = "okay";
};

&be0 {
	status = "okay";
};

&fe0 {
	status = "okay";
};

&de {
	status = "okay";
};

&tcon0 {
	pinctrl-names = "default";
	pinctrl-0 = <&lcd_rgb666_pins>;
	status = "okay";
};

&i2s0 {
	status = "okay";
};

&sound {
	simple-audio-card,name = "HDMIzness";

	/delete-property/ simple-audio-card,routing;

	simple-audio-card,frame-master = <&dai_link_master>;
	simple-audio-card,bitclock-master = <&dai_link_master>;
	simple-audio-card,continuous-clock;

	status = "okay";
};

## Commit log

2020-05-27 sch: Add TDA19988
2020-05-27 sym: Add TS3DV20812
2020-05-27 sch: Add LicheeNano LCD connector
2020-05-28 sch: Main video data path done
2020-05-28 Fix file permissions
2020-05-28 sym: Add LicheeNano symbol
2020-05-28 fp: Add LicheeNano footprint
2020-05-28 sch: Add HDMI 1.8V PSU
2020-05-29 sch: Add HPD handling
2020-05-29 fp: Add the star of the show: the PCB-based HDMI connector
2020-05-29 fp: Add "regular" female HDMI connector
2020-05-29 sch: Misc touches
2020-05-29 fp: Center HDMI footprints
2020-05-29 sch: Add lots of testpoints
2020-05-29 sch: Part number assignment done
2020-05-29 sch: Add symbol for the PCB-based HDMI connector
2020-05-29 fp: Add min width pcb hdmi keepout
2020-05-29 pcb: Placement done
2020-05-29 pcb: Routing done
2020-05-29 Add drone CI
2020-05-30 pcb: Add "this side up" symbol to PCB
2020-06-01 pcb: Fix mistakenly rotated hdmi track
2020-06-01 pcb: Length and skew tuned HDMI pairs
2020-06-01 pcb: Changed layer 3 from +3V3 to GND
2020-06-01 pcb: Add proper diff pair layer transition vias
2020-06-02 fp: Add male HDMI plug 3D model to PCB HDMI connector
2020-06-02 pcb: Add drawing to help with HDMI connector orientation
2020-06-02 pcb: Move LEDs and add silkscreen stuff
2020-06-02 sch, pcb: Add 3V3 and 5V headers
2020-06-02 pcb: Add OSHW logo
2020-06-02 fp, pcb: Fix absolute 3D model path
2020-06-03 pcb: Fix silk for testpads
2020-06-04 sch: Draw wires rather than labels where wiring is straightforward
2020-06-04 *: Add USB-UART chip (CH340C)
2020-06-04 sch, pcb: Add UART0 activity LEDs
2020-06-04 pcb: Fix DRC issues
2020-06-04 sch: Fix real ERC issues
2020-06-04 sch: Add missing P/N for USB-C connector
2020-06-04 Add FPC connector 3D model
2020-06-05 sym, fp, sch: Fix LicheeNano and LCD connector being flipped
2020-06-05 pcb: Reroute PCB following footprint flip
    Bowtie and complicated via thingies are gone now \o/
2020-06-05 pcb: Add Lichee pinout on silk and stich grounds
2020-06-05 pcb: Add lichee orientation to silk
2020-06-05 pcb: Fix solder mask clearance and min width
2020-06-05 pcb: Fix JLC string
    JLCPCB requires the string "JLCJLCJLCJLC" to be specified to control
    where they'll put the order number. One of the four JLC was missing...
2020-07-01 sch: Wire I2S
2020-07-01 doc: Add F1C100s family datasheets and manuals
2020-07-01 pcb: Wire I2S signals
2020-07-01 licheedmi: Release v1.1
2020-07-01 lib: Add SiI9022A symbol
2020-07-01 lib: Make SiI9022 symbol closer to TDA19988
2020-07-01 doc: Add LicheeNano schematic
2020-07-01 sch: Replace TDA19988 with SiI9022A (wip)
2020-07-01 lib: Add TLV743P
2020-07-01 sch: Use 1.2V LDO for SiI and fix auxilary signals
2020-07-01 lib: Tweak SiI9022A pin positions on symbol
2020-07-01 sch: Add extra decoupling cap on AVCC line
2020-07-01 pcb: Route SiI9022A
2020-07-01 fp: Add 3D model for QFN72 used by SiI9022A
2020-07-01 sch: Add missing C17 cap
2020-07-01 Release licheedmi v2.0
2020-07-21 pcb: Refill copper zones
    Because zones were not properly refilled, many signals and power rails
    were shorted to ground internally, meaning no bodge possibility.
2020-07-21 Release licheedmi v2.1
2020-10-17 software: Add buildroot 2020.05 licheepi defconfig
2020-11-14 lib: Add W25Q128JVEIQ
2020-11-14 lib: Add FC-B1010RGBT-HG RGB LED
2020-11-14 lib: Add F1C100s symbol
2020-11-14 hdmizness: Add schematic first draft
2020-11-14 lib: Add PCB-based USB connector
2020-11-14 fp: Add F1C100s footprint
2020-11-14 lib: Add MHPA1515RGBDT
2020-11-14 lib: Add EA3058QDR
2020-11-14 3d: Add 0806 inductor model
2020-11-14 lib: Add 1TS028A-2400-0603-CT
2020-11-14 hdmizness: Use smaller components
2020-11-14 hdmizness: Routing done
2020-11-14 pcb: Add front design
2020-11-14 hdmizness: Add board revision hard straps
2020-11-14 3d: Add missing 3D models
2020-11-15 hdmizness/sch: Add component MFR P/N and LCSC P/N
2020-11-15 lib: Add missing F1C100s 3D model
2020-11-15 ci: Setup both licheedmi and hdmizness build
2020-11-15 ci: Slight tweak
2020-11-15 hdmizness: pcb: Add JLCPCB-specific string to set order number posision
2020-11-15 hdmizness: Redo HDMI part with SiI9022A
    Since I have a stock of 25 of both ICs...
2020-12-09 soft: Add buildroot submodule
2021-03-15 soft: Add first working, booting version
    This includes basic Buildroot, U-Boot and Linux configs to get Linux
    booting on the board
2021-03-21 software: Add fbdoom package
2021-03-25 software: Fix USB det pin in dts
2021-03-25 software: Add working USB OTG + video Linux defconfig
2021-03-25 software: Remove stray buildroot config
2021-03-25 software/fbdoom: Add patch for MUCH faster draw routine
    This is a ~6x speedup, making the game run at 20fps rather than 3 at
    720p output
2021-04-13 software/config: Upgrade to Linux 5.11.10
2021-04-13 software/config: Set root password to allow SSH into the businesscard
2021-04-14 software: Lighten up config to free up flash space
    I doubt the full vim runtime is terribly useful on this card... I even
    doubt vim itself is useful...
2021-04-14 software: Fix fbdoom build depending on SDL
2021-04-14 software: Add post-build script to generate SSH keys
2022-04-20 software: Add sample files in board overlay
2022-04-20 software: Add missing mtd-tools to host packages
2022-04-20 software: Add readme with build and flash instructions
2023-01-03 software: update to kernel 6.1
    This may require a buildroot upgrade, untested.
2023-01-03 software: upgrade to buildroot 2022.11
2023-01-03 software: upgrade to U-Boot 2022.10
    and it's mainline, yay!
2023-07-21 software: add Makefile
2023-07-21 Add random notes file
2023-07-21 software: add fakeroot patch for recent gcc versions
2023-09-01 software: fix defconfig following buildroot update
2023-09-18 software: add uinput support to fbdoom
2025-02-25 Revert "software: update to kernel 6.1"
    This reverts commit 781f05e8d4e4902e49adceafee3f10f4798b9524.
    Video output is broken on 6.1. Which is a shame since this is the value
    proposition of this project.
2025-02-25 software/makefile: add flash target
    Help my memory by not remembering every fringgin time what the command
    is.
2025-02-25 software: add kbdsrv to have some input
2025-02-25 software: add network configuration
    Make the card be detected as an USB-Ethernet adapter, start Dropbear and
    dnsmasq, and tada!
2025-02-26 software: finally boot to DOOM
2025-02-26 software: add motd message at boot on console
2025-02-26 software: pick output resolution based on CPU
    The F1C200s has 64MB of RAM, and is able to do a 720p output, which the
    F1C100s cannot with its 32MB.
    Determine the memory size by checking whether the address space wraps at
    32MB or not (thanks U-Boot for printing this to the console, but not
    exposing it to scripts).
2025-03-22 hardware: back-import v1 in its own folder
2025-03-22 hardware: update to KiCAD 9.0
2025-03-22 hardware: don't put soldermask in front of pcb connectors
2025-04-04 hardware: make front text be exposed copper
    The boards are black, I'm doing ENIG, that'll look great. And text will
    be much more precise using soldermask aperture instead of silkscreen.
2025-04-04 hardware: update bom with chips now on LCSC
    F1C100s, SiI9022A and TDA19988 are now available on LCSC. Set the proper
    fields to show them on the BoM.
2025-04-04 software: enable uinput in the kernel
2025-04-04 software/overlay: fix USB init script
2025-04-04 software: make sound work
    The grunt of the work is actually in the linux repo, where the fix that
    took me so long to find is written. Oh well.
2025-05-05 software: switch to FBDoom from my own fork
2025-05-19 software/dts: don't forget to enable display frontend
2025-05-19 software/config: use musl instead of glibc and enable optimizations
2025-05-19 software/config: don't bother with linux with audio codec
    The board outputs audio through HDMI, which uses I2S, which does not
    need the codec.
2025-05-19 software/config: configure correct kernel headers version
2025-05-19 software: use correct SPI pin names in U-Boot device tree
2025-05-19 software: update to buildroot 2025.02.3
2025-05-23 software: update to U-Boot 2025.01
    In addition to being much more recent, this U-Boot version has the nice
    taste of being much much faster loading the kernel from the SPI flash,
    making the card boot time acceptable.
2025-05-23 software: upgrade to Linux 6.14
2025-05-23 software: build and install kbdsrv
    For some reason, this was wissing :shrug:

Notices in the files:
hardware/hdmizness-v1/hdmizness.kicad_pcb:
v1.0 - (c) 2020
